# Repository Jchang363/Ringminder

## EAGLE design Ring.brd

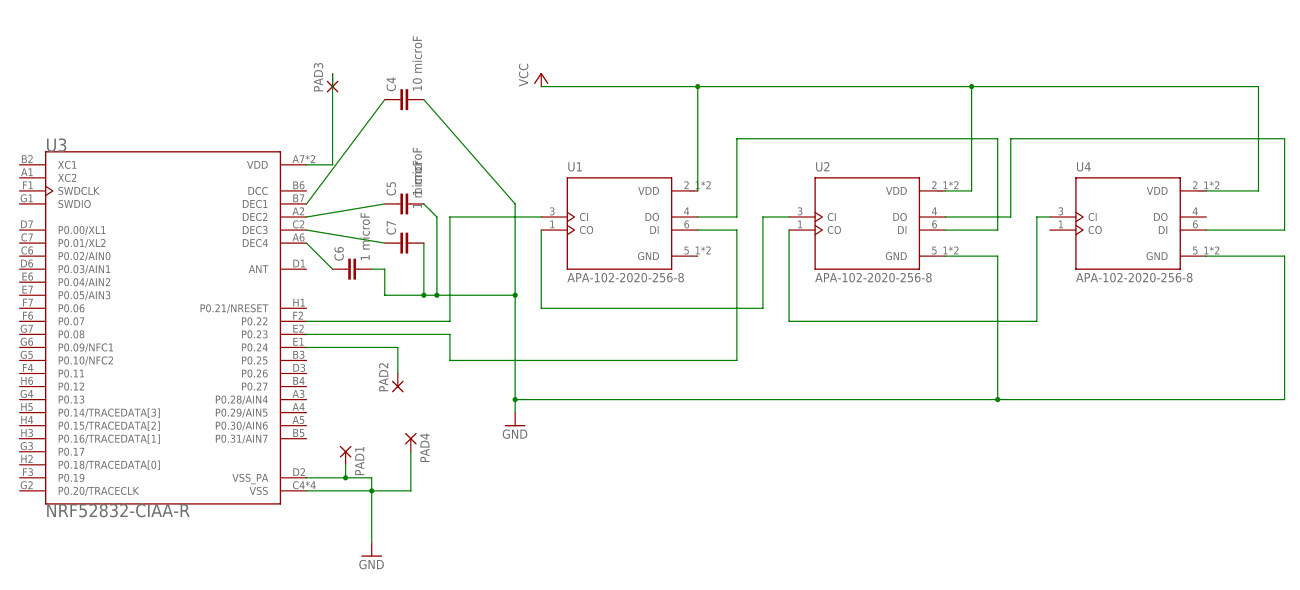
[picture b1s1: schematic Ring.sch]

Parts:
C4: 10 microF; C2.5-3
C5, C6, C7: 1 microF; C2.5-3
PAD1, PAD2, PAD3, PAD4: 1,6/0,8
U1, U2, U4: APA-102-2020-256-8; LED_APA-102-2020-256-8
U3: NRF52832-CIAA-R; BGA50N40P7X8_300X320X40

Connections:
DCC: U3.B6 (DCC)
GND: C4.2, C5.2, C6.2, C7.2, PAD1.1, PAD4.1, U1.5_1 (GND), U1.5_2 (GND), U2.5_1 (GND), U2.5_2 (GND), U3.C4 (VSS), U3.C5 (VSS), U3.D2 (VSS_PA), U3.E3 (VSS), U3.F5 (VSS), U4.5_1 (GND), U4.5_2 (GND)
unnamed: U1.1 (CO), U2.3 (CI)
unnamed: U1.3 (CI), U3.F2 (P0.22)
unnamed: U1.6 (DI), U3.E2 (P0.23)
unnamed: U1.4 (DO), U2.6 (DI)
unnamed: U2.1 (CO), U4.3 (CI)
unnamed: U2.4 (DO), U4.6 (DI)
unnamed: PAD2.1, U3.E1 (P0.24)
unnamed: PAD3.1, U3.A7 (VDD), U3.H7 (VDD)
unnamed: C4.1, U3.B7 (DEC1)
unnamed: C5.1, U3.A2 (DEC2)
unnamed: C7.1, U3.C2 (DEC3)
unnamed: C6.1, U3.A6 (DEC4)
VCC: U1.2_1 (VDD), U1.2_2 (VDD), U2.2_1 (VDD), U2.2_2 (VDD), U4.2_1 (VDD), U4.2_2 (VDD)

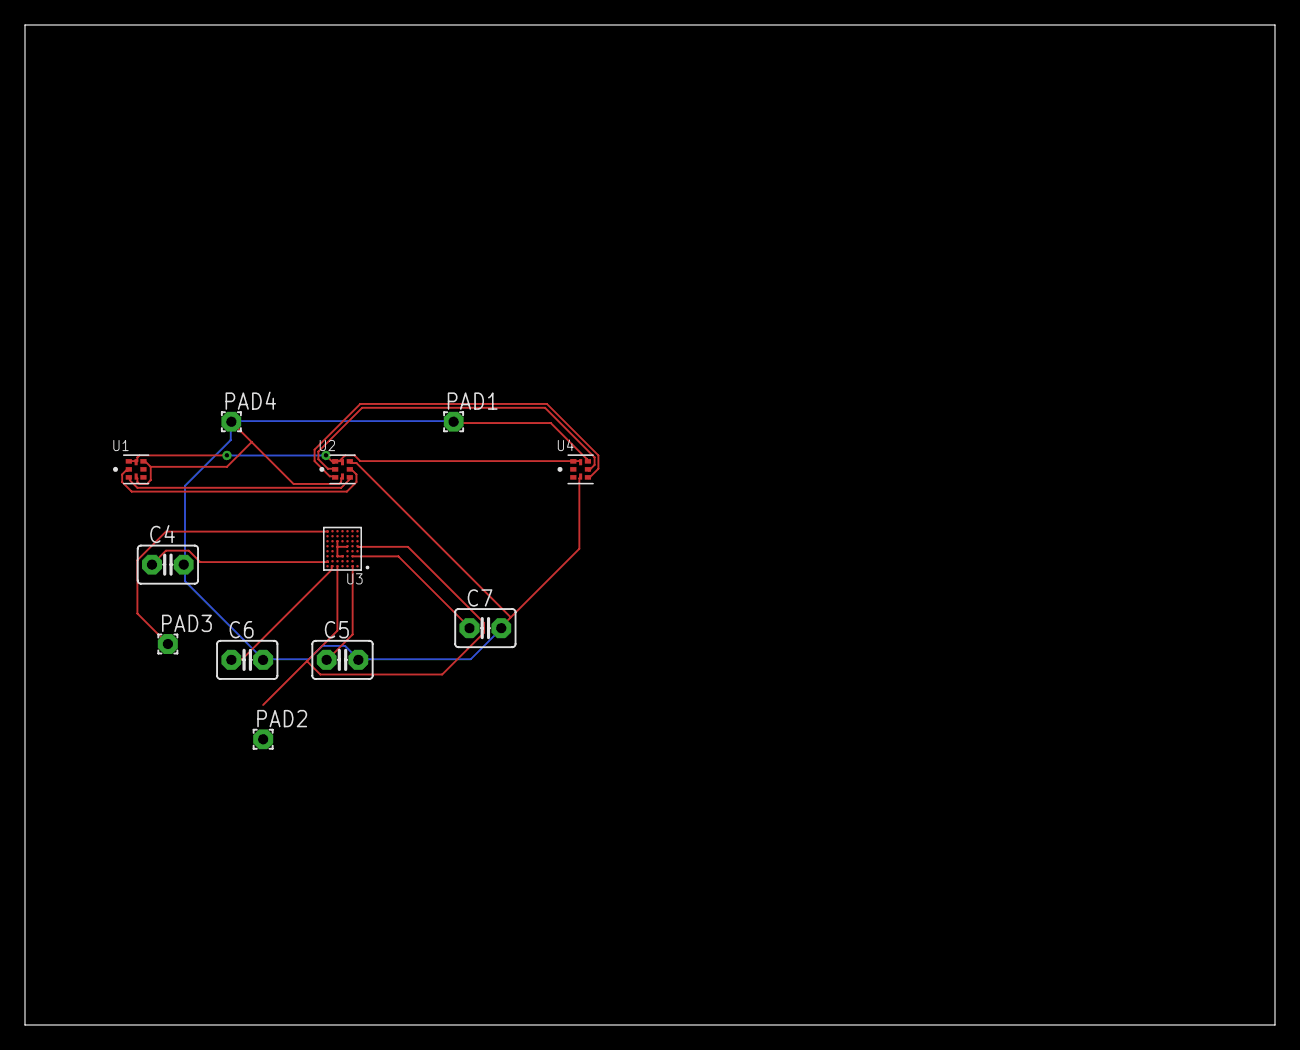
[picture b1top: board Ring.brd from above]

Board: 2 copper layers, 100.0 x 80.0 mm, 12 parts (0 on the bottom side), 14 nets.

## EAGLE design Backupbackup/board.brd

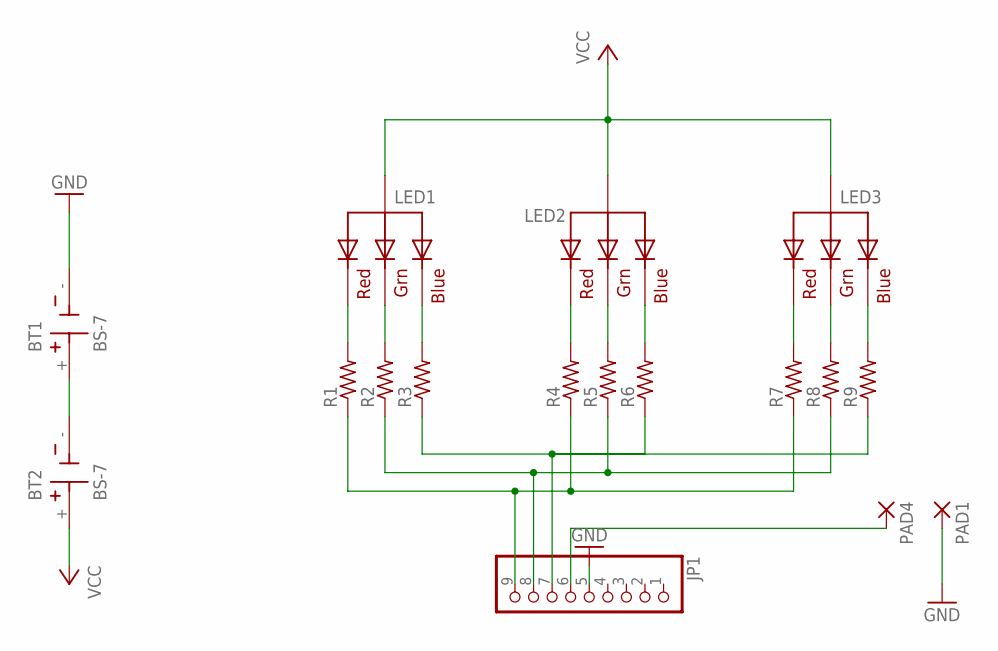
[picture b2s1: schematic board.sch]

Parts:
BT1, BT2: BS-7; BAT_BS-7
JP1: PINHD-1X9; 1X09-BIG
LED1, LED2, LED3: RGBLED_CA-5MM; LED5MMRGB
PAD1, PAD4: 1,6/0,8
R1, R2, R3, R4, R5, R6, R7, R8, R9: R-US_0207/7; 0207/7

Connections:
GND: BT1.-, JP1.5, PAD1.1
unnamed: BT1.+, BT2.-
unnamed: LED3.1 (RED), R7.2
unnamed: LED3.3 (GREEN), R8.2
unnamed: LED1.1 (RED), R1.2
unnamed: LED1.3 (GREEN), R2.2
unnamed: LED1.4 (BLUE), R3.2
unnamed: LED2.1 (RED), R4.2
unnamed: LED2.3 (GREEN), R5.2
unnamed: LED2.4 (BLUE), R6.2
unnamed: LED3.4 (BLUE), R9.2
unnamed: JP1.9, R1.1, R4.1, R7.1
unnamed: JP1.6, PAD4.1
unnamed: JP1.8, R2.1, R5.1, R8.1
unnamed: JP1.7, R3.1, R6.1, R9.1
VCC: BT2.+, LED1.2 (VCC), LED2.2 (VCC), LED3.2 (VCC)

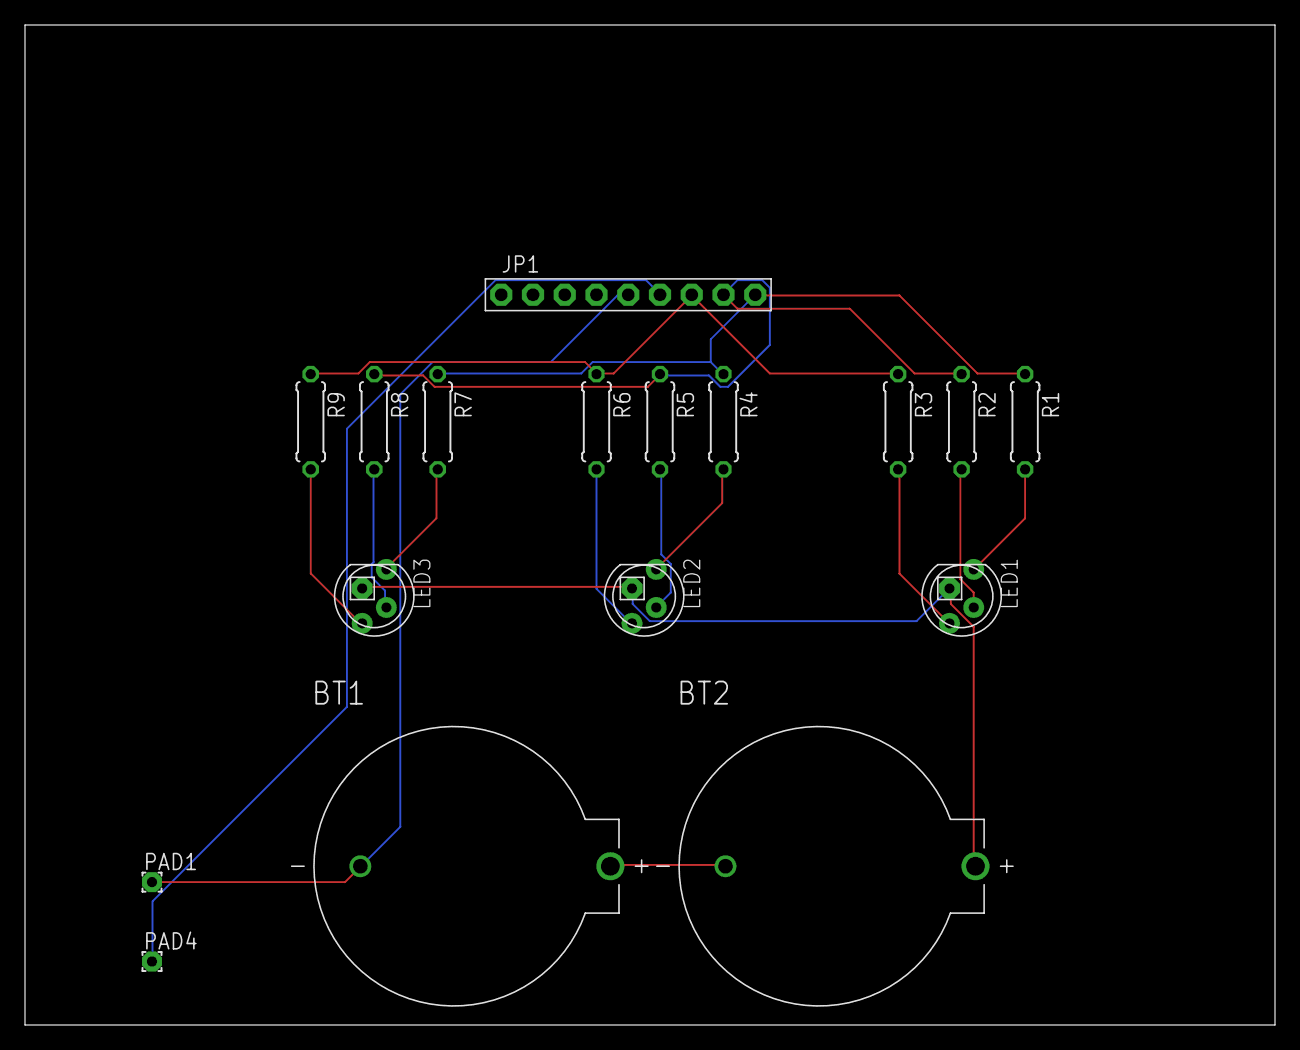
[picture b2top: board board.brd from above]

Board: 2 copper layers, 100.0 x 80.0 mm, 17 parts (0 on the bottom side), 16 nets.

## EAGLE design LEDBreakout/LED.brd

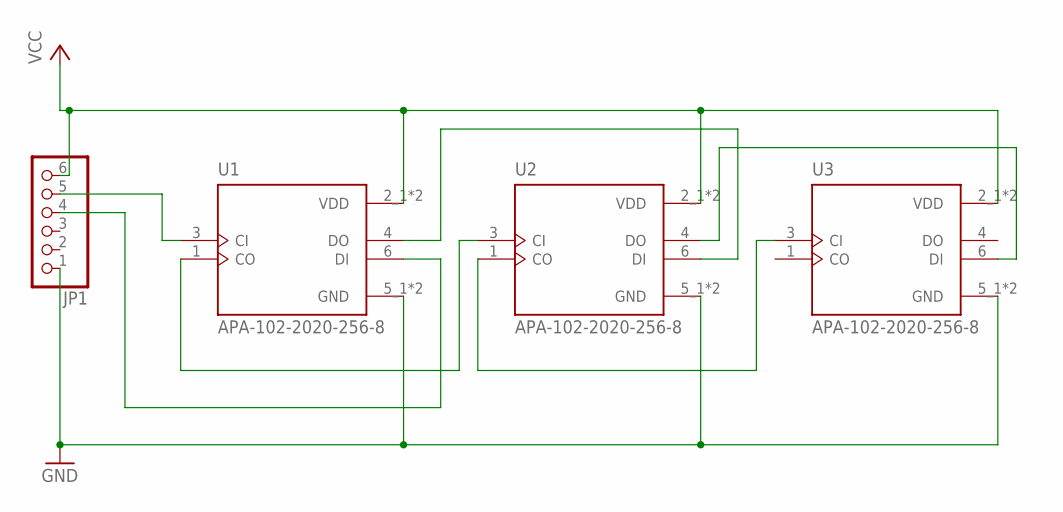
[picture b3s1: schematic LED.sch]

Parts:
JP1: PINHD-1X6CLEAN; 1X06-CLEAN
U1, U2, U3: APA-102-2020-256-8; LED_APA-102-2020-256-8

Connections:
GND: JP1.1, U1.5_1 (GND), U1.5_2 (GND), U2.5_1 (GND), U2.5_2 (GND), U3.5_1 (GND), U3.5_2 (GND)
unnamed: JP1.5, U1.3 (CI)
unnamed: JP1.4, U1.6 (DI)
unnamed: U1.1 (CO), U2.3 (CI)
unnamed: U1.4 (DO), U2.6 (DI)
unnamed: U2.4 (DO), U3.6 (DI)
unnamed: U2.1 (CO), U3.3 (CI)
VCC: JP1.6, U1.2_1 (VDD), U1.2_2 (VDD), U2.2_1 (VDD), U2.2_2 (VDD), U3.2_1 (VDD), U3.2_2 (VDD)

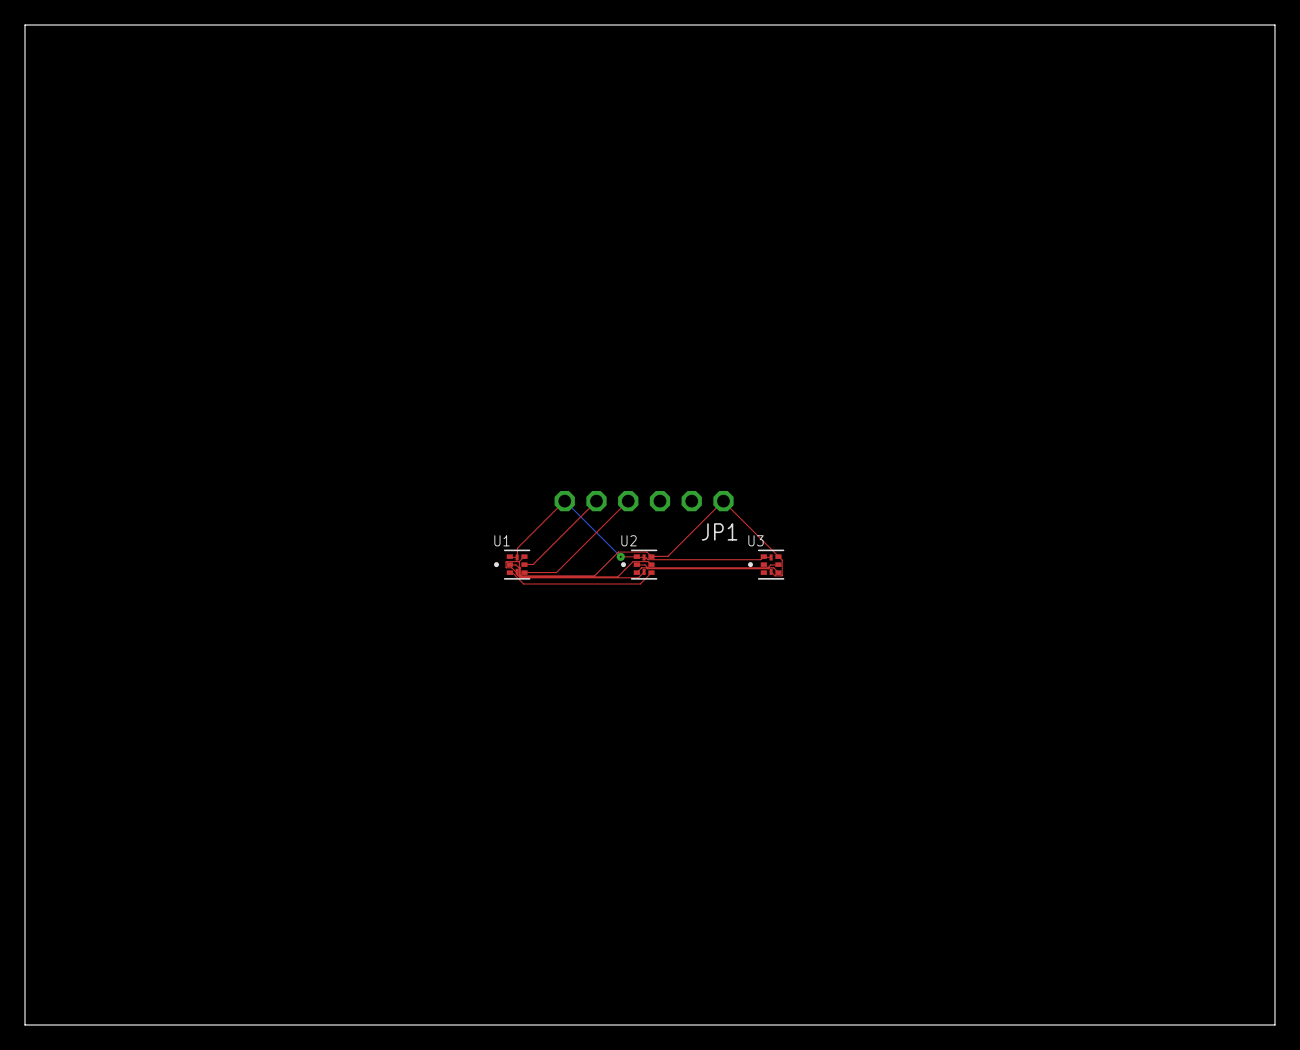
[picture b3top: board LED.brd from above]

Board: 2 copper layers, 100.0 x 80.0 mm, 4 parts (0 on the bottom side), 8 nets.

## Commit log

2022-10-07 Added libraries and schematics
    EM bluetooth
    MSP430 MCU
    TI battery management
2022-10-07 Added new libraries
2022-10-07 Added NRF52840 datasheet and library
2022-10-11 Added NRF52382, BQ25, and connections
2022-10-12 Updated connections, deleted bluetooth module
2022-10-21 board files
2022-10-21 Added breakout boards
2022-10-26 updated led breakout
2022-10-26 Added LED library
2022-10-26 Created New schemtatic
2023-02-25 projects added
    added projects

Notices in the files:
parts and their libraries:
microbuilder: This work is placed in the public domain, and may be freely used for commercial and non-commercial work with the following conditions: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
